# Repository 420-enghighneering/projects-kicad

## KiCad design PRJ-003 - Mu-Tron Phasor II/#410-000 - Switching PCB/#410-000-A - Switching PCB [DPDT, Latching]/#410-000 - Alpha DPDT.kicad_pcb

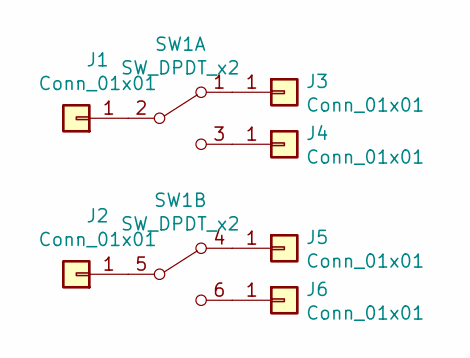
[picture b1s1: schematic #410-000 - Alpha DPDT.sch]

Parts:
J1, J2, J3, J4, J5, J6: Conn_01x01; E_WIRE_PAD
SW1: SW_DPDT_x2; SW_Alpha_Taiwan_SF12020F-0202-20R-L-011

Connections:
unnamed: J1.1, SW1.2 (B)
unnamed: J2.1, SW1.5 (B)
unnamed: J3.1, SW1.1 (A)
unnamed: J4.1, SW1.3 (C)
unnamed: J5.1, SW1.4 (A)
unnamed: J6.1, SW1.6 (C)

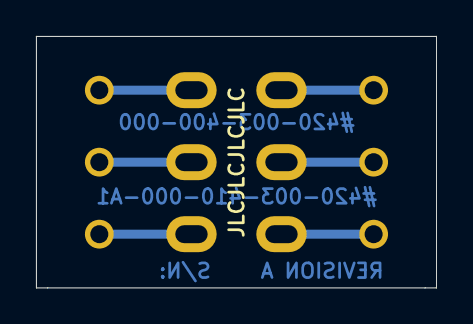
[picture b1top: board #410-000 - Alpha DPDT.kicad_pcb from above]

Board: 2 copper layers, 22.2 x 14.0 mm, 7 parts (0 on the bottom side), 6 nets.

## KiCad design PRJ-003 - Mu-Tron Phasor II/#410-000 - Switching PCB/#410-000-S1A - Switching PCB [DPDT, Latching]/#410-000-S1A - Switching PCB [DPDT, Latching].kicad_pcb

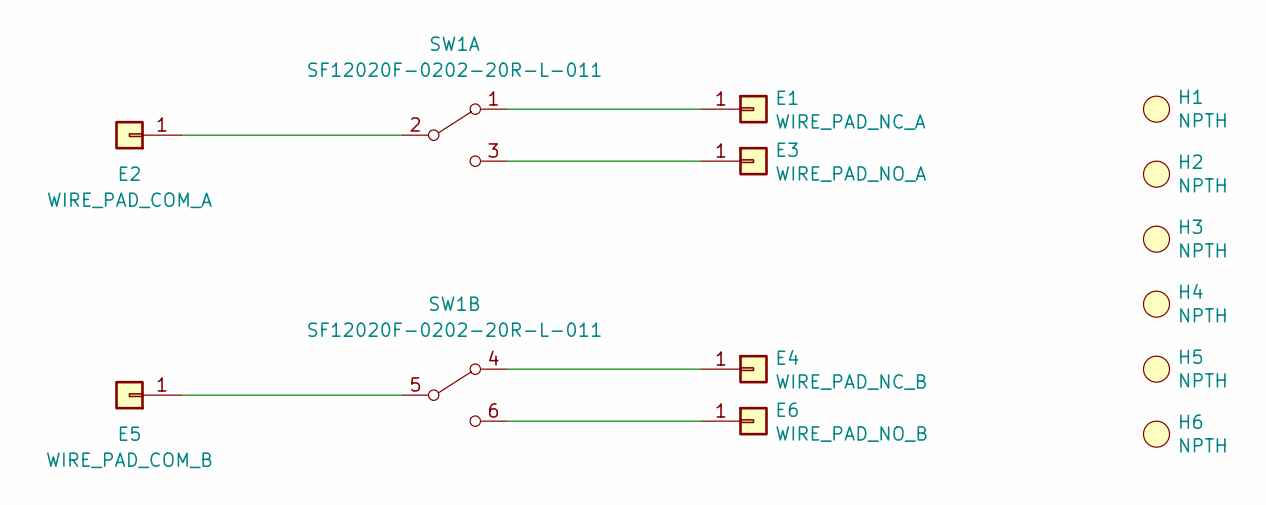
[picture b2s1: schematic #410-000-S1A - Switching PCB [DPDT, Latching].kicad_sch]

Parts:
E1: WIRE_PAD_NC_A; E_WIRE_PAD
E2: WIRE_PAD_COM_A; E_WIRE_PAD
E3: WIRE_PAD_NO_A; E_WIRE_PAD
E4: WIRE_PAD_NC_B; E_WIRE_PAD
E5: WIRE_PAD_COM_B; E_WIRE_PAD
E6: WIRE_PAD_NO_B; E_WIRE_PAD
H1, H2, H3, H4, H5, H6: NPTH; E_ZIPTIE_NPTH_2x_P2.54mm
SW1: SF12020F-0202-20R-L-011; SW_Alpha_Taiwan_SF12020F-0202-20R-L-011_BFCU

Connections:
unnamed: E1.1, SW1.1 (A)
unnamed: E2.1, SW1.2 (B)
unnamed: E3.1, SW1.3 (C)
unnamed: E4.1, SW1.4 (A)
unnamed: E5.1, SW1.5 (B)
unnamed: E6.1, SW1.6 (C)

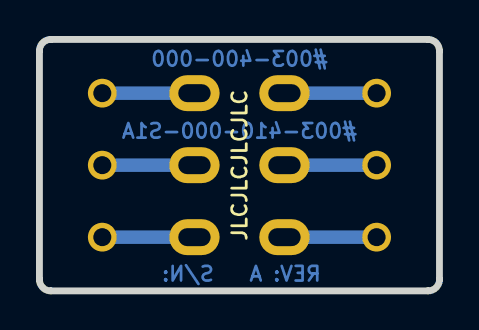
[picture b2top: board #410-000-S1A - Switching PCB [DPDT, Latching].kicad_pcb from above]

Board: 2 copper layers, 22.2 x 14.0 mm, 13 parts (0 on the bottom side), 6 nets.

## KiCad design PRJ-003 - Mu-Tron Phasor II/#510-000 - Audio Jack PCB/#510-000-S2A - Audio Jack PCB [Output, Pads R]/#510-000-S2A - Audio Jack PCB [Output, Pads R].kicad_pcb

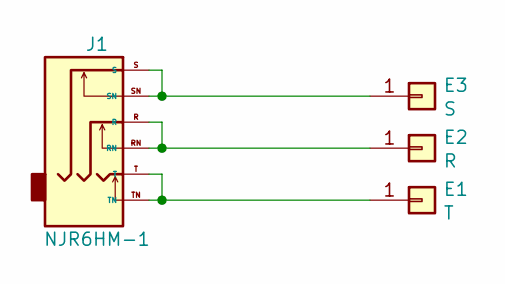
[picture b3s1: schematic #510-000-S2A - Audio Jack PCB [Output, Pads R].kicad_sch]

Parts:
E1: T; E_WIRE_PAD_1x_ZIPTIE_NPTH_2x_NARROW
E2: R; E_WIRE_PAD_1x_ZIPTIE_NPTH_2x_NARROW
E3: S; E_WIRE_PAD_1x_ZIPTIE_NPTH_2x_NARROW
J1: NJR6HM-1; J_AC_NOCHASSIS

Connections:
unnamed: E1.1, J1.T, J1.TN
unnamed: E2.1, J1.R, J1.RN
unnamed: E3.1, J1.S, J1.SN

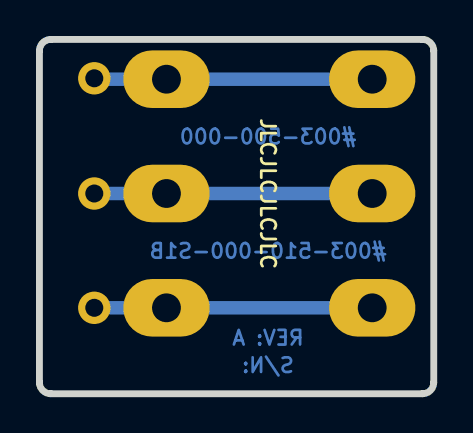
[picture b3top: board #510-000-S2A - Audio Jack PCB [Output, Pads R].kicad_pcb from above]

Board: 2 copper layers, 21.9 x 19.7 mm, 4 parts (0 on the bottom side), 3 nets.

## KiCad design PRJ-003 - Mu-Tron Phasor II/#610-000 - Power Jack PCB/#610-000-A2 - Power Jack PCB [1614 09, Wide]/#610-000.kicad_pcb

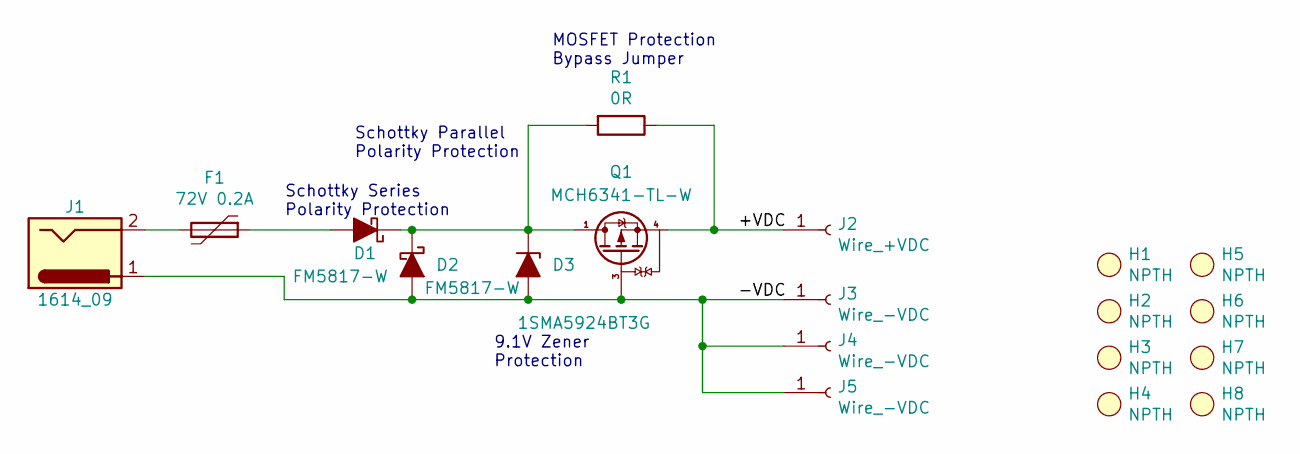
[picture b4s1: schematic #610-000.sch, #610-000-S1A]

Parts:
D1, D2: FM5817-W; Rectron_FM5817-W
D3: 1SMA5924BT3G; ON_Semi_1SMA5924BT3G
F1: 72V 0.2A; R_CC25_P5.08_V
H1, H2, H3, H4, H5, H6, H7, H8: NPTH; E_ZIPTIE_NPTH
J1: 1614_09; J_POWER_SMALL
J2: Wire_+VDC; E_WIRE_PAD
J3, J4, J5: Wire_-VDC; E_WIRE_PAD
Q1: MCH6341-TL-W; ON_Semi_MCH6341-TL-W
R1: 0R; R_0603_1608M

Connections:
/+VDC: J2.1, Q1.4 (S), R1.1
/-VDC: D2.1 (A), D3.1 (A), J1.1, J3.1, J4.1, J5.1, Q1.3 (G)
unnamed: D1.1 (A), F1.1
unnamed: D1.2 (K), D2.2 (K), D3.2 (K), Q1.1 (D), Q1.2 (D), Q1.5 (D), Q1.6 (D), R1.2
unnamed: F1.2, J1.2

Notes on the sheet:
9.1V Zener Protection
Schottky Series Polarity Protection
Schottky Parallel Polarity Protection
MOSFET Protection Bypass Jumper

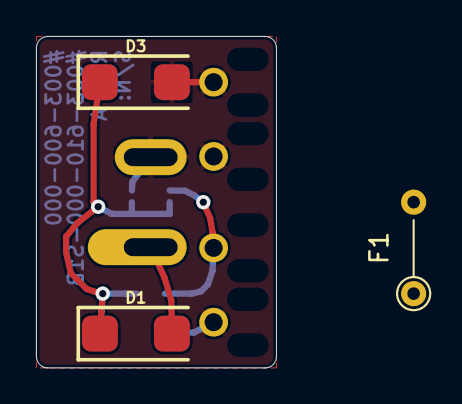
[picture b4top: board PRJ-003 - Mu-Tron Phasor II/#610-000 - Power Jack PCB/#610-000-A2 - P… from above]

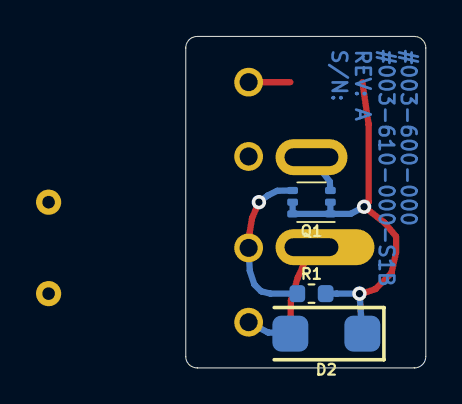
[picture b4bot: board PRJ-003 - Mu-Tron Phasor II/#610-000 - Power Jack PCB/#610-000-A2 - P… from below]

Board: 2 copper layers, 13.3 x 18.4 mm, 19 parts (7 on the bottom side), 5 nets.

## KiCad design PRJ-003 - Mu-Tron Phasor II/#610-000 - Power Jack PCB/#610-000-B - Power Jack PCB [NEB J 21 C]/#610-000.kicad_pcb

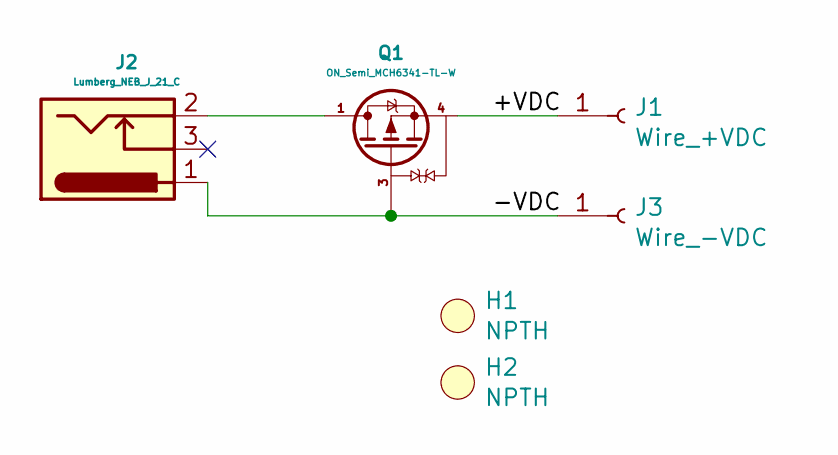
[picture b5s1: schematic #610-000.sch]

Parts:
H1, H2: NPTH; E_ZIPTIE_NPTH
J1: Wire_+VDC; E_WIRE_PAD
J2: Lumberg_NEB_J_21_C; J_DC
J3: Wire_-VDC; E_WIRE_PAD
Q1: ON_Semi_MCH6341-TL-W

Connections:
/+VDC: J1.1, Q1.4 (S)
/-VDC: J2.1, J3.1, Q1.3 (G)
unnamed: J2.2, Q1.1 (D), Q1.2 (D), Q1.5 (D), Q1.6 (D)

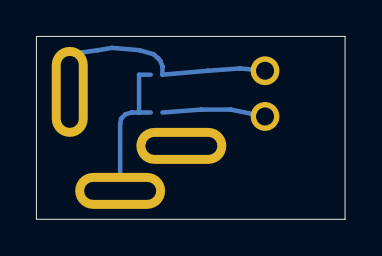
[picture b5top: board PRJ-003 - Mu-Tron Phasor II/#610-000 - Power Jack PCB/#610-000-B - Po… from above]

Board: 2 copper layers, 17.1 x 10.2 mm, 6 parts (1 on the bottom side), 3 nets.

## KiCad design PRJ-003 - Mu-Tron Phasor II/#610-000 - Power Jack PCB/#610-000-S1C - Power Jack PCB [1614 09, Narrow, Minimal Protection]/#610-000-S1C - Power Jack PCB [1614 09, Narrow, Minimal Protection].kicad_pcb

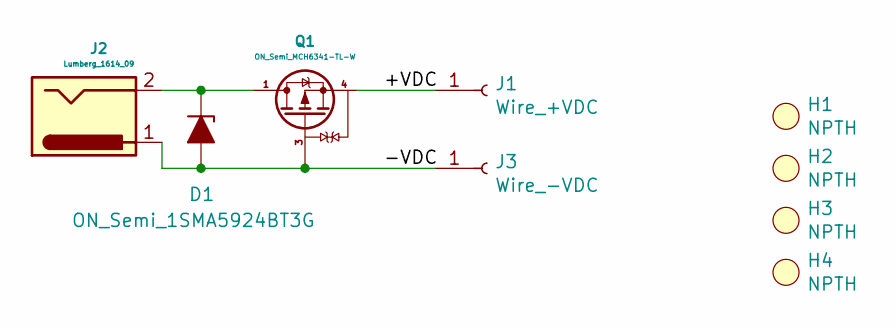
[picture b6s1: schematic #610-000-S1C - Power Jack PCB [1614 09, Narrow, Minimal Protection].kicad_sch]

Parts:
D1: ON_Semi_1SMA5924BT3G
H1, H2, H3, H4: NPTH; E_ZIPTIE_NPTH
J1: Wire_+VDC; E_WIRE_PAD
J2: Lumberg_1614_09; J_POWER_SMALL
J3: Wire_-VDC; E_WIRE_PAD
Q1: ON_Semi_MCH6341-TL-W

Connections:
/+VDC: J1.1, Q1.4 (S)
/-VDC: D1.1 (A), J2.1, J3.1, Q1.3 (G)
unnamed: D1.2 (K), J2.2, Q1.1 (D), Q1.2 (D), Q1.5 (D), Q1.6 (D)

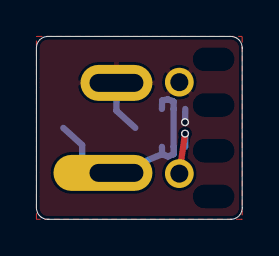
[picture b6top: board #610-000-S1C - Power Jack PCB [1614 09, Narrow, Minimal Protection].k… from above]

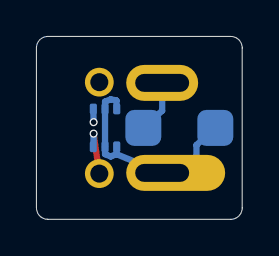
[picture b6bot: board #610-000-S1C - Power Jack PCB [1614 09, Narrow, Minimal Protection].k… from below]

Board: 2 copper layers, 11.4 x 10.2 mm, 9 parts (4 on the bottom side), 3 nets.
